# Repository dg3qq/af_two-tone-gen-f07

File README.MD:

# AF-TWO-TONE-GENERATOR

##### cc-by-sa-nc DG3QQ rodi
##### rev. mar. 2024

# Bastel-Projekt zum 14. Giessener Amateurfunk Tag

+ [expose](F07-project/_expose.md]
+ video interview by Kirk (DO3KI) [14. Gießener Amateurfunktreffen 2024 - Doppeltongenerator Bauprojekt & ARRL Prüfung USA Rufzeichen](https://www.youtube.com/watch?v=AF0V_h3_ksM)

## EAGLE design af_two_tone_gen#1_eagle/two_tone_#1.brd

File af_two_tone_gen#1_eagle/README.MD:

# Two-Tone-Generator by DG3QQ 

#### copyright: dg3qq (cc-by-sa-nc)

## PCB in EagleCad 

To get around delays, I resorted to a *free* version of EagleCad (6.xx).

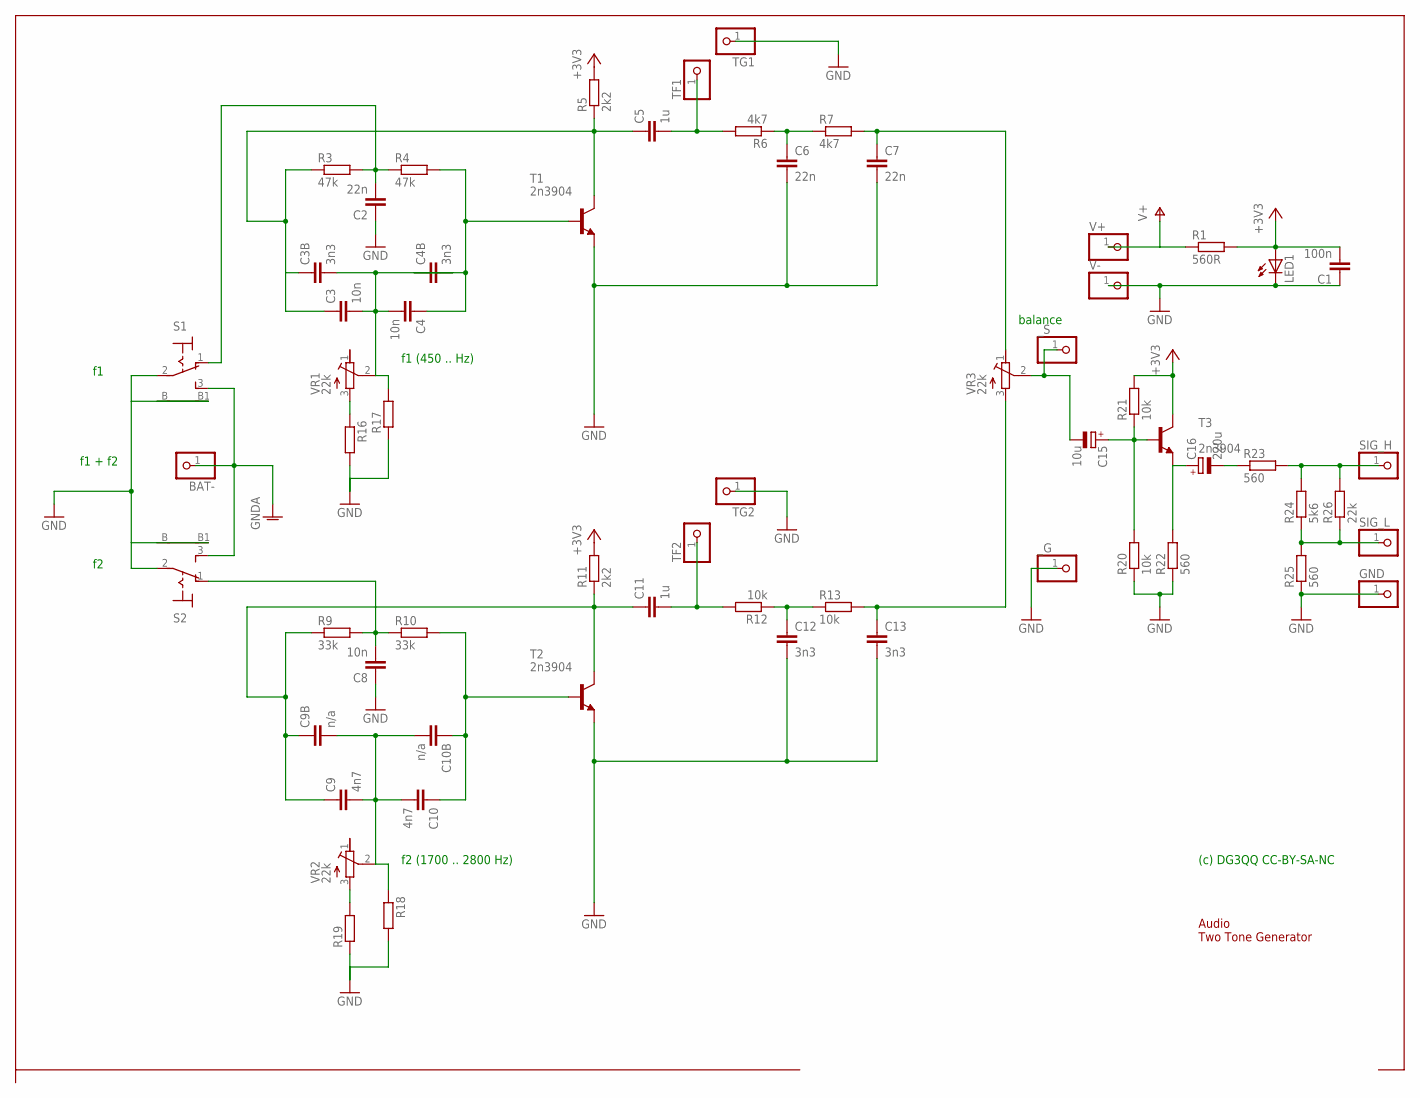
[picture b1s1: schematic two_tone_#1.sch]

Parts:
BAT-: PINHD-1X1; 1X01
C1: 100n; C025_050-025X075
C2, C6, C7: 22n; C025_050-025X075
C3, C4, C8: 10n; C025_050-025X075
C3B, C4B, C12, C13: 3n3; C025_050-025X075
C5, C11: 1u; C025_050-025X075
C9, C10: 4n7; C025_050-025X075
C9B, C10B: n/a; C025_050-025X075
C15: 10u; E2,5-5
C16: 220u; E5-10,5
GND: PINHD-1X1; 1X01
LED1: LED3MM
R1: 560R; 0207/2V
R3: 47k; 0207/10
R4: 47k; 0207/2V
R5, R11: 2k2; 0207/2V
R6, R7: 4k7; 0207/2V
R9: 33k; 0207/10
R10: 33k; 0207/2V
R12, R13, R20, R21: 10k; 0207/2V
R16, R17, R18, R19: R-EU_0207/2V; 0207/2V
R22, R23, R25: 560; 0207/2V
R24: 5k6; 0207/2V
R26: 22k; 0207/2V
S1, S2: 9070-1W
SIG_H: PINHD-1X1; 1X01
SIG_L: PINHD-1X1; 1X01
T1, T2, T3: 2n3904; TO92-EBC
TF1, TF2: PINHD-1X1; 1X01
TG1, TG2: PINHD-1X1; 1X01
V+: PINHD-1X1; 1X01
V-: PINHD-1X1; 1X01
VR1, VR2, VR3: 22k; SPINDLE_414S6
_G: PINHD-1X1; 1X01
_S: PINHD-1X1; 1X01

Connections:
+3V3: C1.2, LED1.A, R1.2, R5.2, R11.2, R21.2, T3.C
BAT-: BAT-.1, S1.3 (S), S2.3 (S)
GND: C1.1, C2.1, C6.2, C7.2, C8.1, C12.2, C13.2, GND.1, LED1.K (C), R16.2, R17.1, R18.2, R19.1, R20.1, R22.1, R25.1, S1.2, S1.B, S1.B1, S2.2, S2.B, S2.B1, T1.E, T2.E, TG1.1, TG2.1, V-.1, _G.1
unnamed: C5.2, R6.2, TF1.1
unnamed: C6.1, R6.1, R7.1
unnamed: C2.2, R3.2, R4.1, S1.1 (O)
unnamed: C4.1, C4B.1, R4.2, T1.B
unnamed: C3.1, C3B.1, C5.1, R3.1, R5.1, T1.C
unnamed: C3.2, C3B.2, C4.2, C4B.2, R17.2, VR1.2 (S)
unnamed: C7.1, R7.2, VR3.1 (A)
unnamed: C8.2, R9.2, R10.1, S2.1 (O)
unnamed: C10.1, C10B.1, R10.2, T2.B
unnamed: C9.1, C9B.1, C11.1, R9.1, R11.1, T2.C
unnamed: C9.2, C9B.2, C10.2, C10B.2, R18.1, VR2.2 (S)
unnamed: C11.2, R12.2, TF2.1
unnamed: C12.1, R12.1, R13.1
unnamed: C13.1, R13.2, VR3.3 (E)
unnamed: R19.2, VR2.3 (E)
unnamed: C15.+, R20.2, R21.1, T3.B
unnamed: C15.-, VR3.2 (S), _S.1
unnamed: R16.1, VR1.3 (E)
unnamed: C16.+, R22.2, T3.E
unnamed: C16.-, R23.1
unnamed: R23.2, R24.2, R26.2, SIG_H.1
unnamed: R24.1, R25.2, R26.1, SIG_L.1
V+: R1.1, V+.1

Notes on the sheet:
balance
f1 (450 .. Hz)
f2 (1700 .. 2800 Hz)
f1 + f2
(c) DG3QQ CC-BY-SA-NC
Audio Two Tone Generator

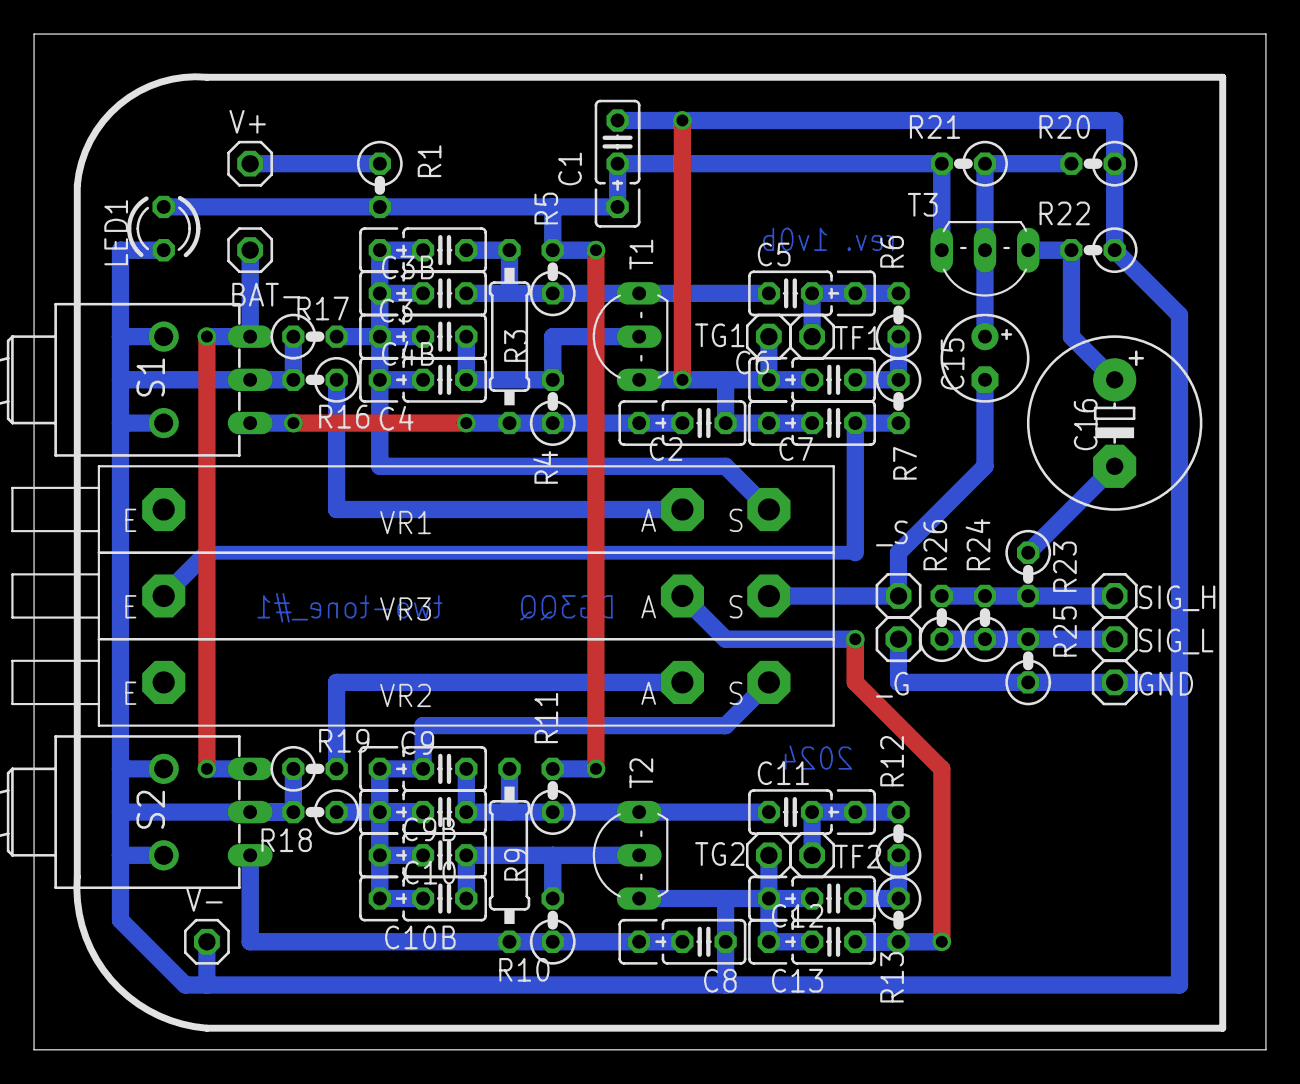
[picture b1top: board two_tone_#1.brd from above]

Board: 2 copper layers, 72.4 x 59.7 mm, 62 parts (0 on the bottom side), 26 nets.

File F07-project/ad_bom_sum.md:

# Two Tone Generator - DARC F07 Project (c) DG3QQ

#####  Doc-Rev: 20240224-1350

## Stückliste - Bill Of Materials

### Widerstände - Resitors 
| check | Qty  | type/value | id | comment |
| :---  | ---: | :--- | :--- | :--- |
| [___] | 4 | 560 0,25W | R1, R22, R23, R25 | . |
| [___] | 2 | 2k2 0,25W | R5, R11| . |
| [___] | 2 | 4k7 0,25W | R6, R7| . |
| [___] | 1 | 5k6 0,25W | R24 | . |
| [___] | 4 | 10k 0,25W | R12, R13, R20, R21| . |
| [___] | 1 | 22k 0,25W | R26 | . |
| [___] | 2 | 33k 0,25W | R9 R10| . |
| [___] | 2 | 47k 0,25W | R3, R4| . |
| [___] | 2 | 0R | R16, R19 | Brücke mit langen Enden (Harnadelform) |
|       | 2 | na | R17, R18 | . |

 
### Kondensatoren - Capacitors
| check | Qty  | type/value | id | comment |
| :---  | ---: | :--------- | :--- | :--- |
| [___] | 4 | 3n3 (332) | C3B, C4B, C12, C13 | . |
| [___] | 2 | 4n7 (472) | C9, C10| . |
| [___] | 3 | 10n (103) | C3, C4, C8 | . |
| [___] | 3 | 22n (223) | C2, C6, C7 | . |
| [___] | 1 | 100n (104) | C1 | . |
| [___] | 2 | 1µ0 (105) | C5, C11 | . |


### Elektrolyt-Kondensator - Elko
| check | Qty  | type/value | id | comment |
| :---  | ---: | :--- | :--- | :--- |
| [___] | 1 | 10µF 16V radial | C15 | . |
| [___] | 1 | 220µF 25V radial | C16 | . | 


### Transistoren - Transistors 
| check | Qty | type/value | id | comment |
| :---  | ---: | :--- | :--- | :--- |
| [___] | 3 | NPN SI-Transistor 2N3904 | T1, T2, T3 | o.ä. |


### Diodes - Dioden (LED) 
| check | Qty | type/value | id | comment |
| :---  | ---: | :--- | :--- | :--- |
| [___] | 1 | LED blue ø3mm | LED1 | EVERSTAR R3040HBDE034 |

### Potentiometer 
| check | Qty | type/value | id | comment |
| :---  | ---: | :--- | :--- | :--- |
| [___] | 3 | 22k/20turn trimpot.| VR1, VR2, VR3  | . |

### ... div.
| check | Qty | type/value  | id | comment |
| :---  | ---: | :--- | :--- | :--- |
| [___] | 2 | miniature switch SPST | S1, S2 | MTS-102-A1 |
| [___] | 3 | Buchsenleiste 1x2 pin | TF1, TF2, _S | |
| [___] | 1 | Buchsenleiste 1x3 pin | TFO | . |
| [___] | 1 | PCB                  | x1 | AllPCB |
| [___] | 1 | Batteriehalter 3xAAA | x2 | . |

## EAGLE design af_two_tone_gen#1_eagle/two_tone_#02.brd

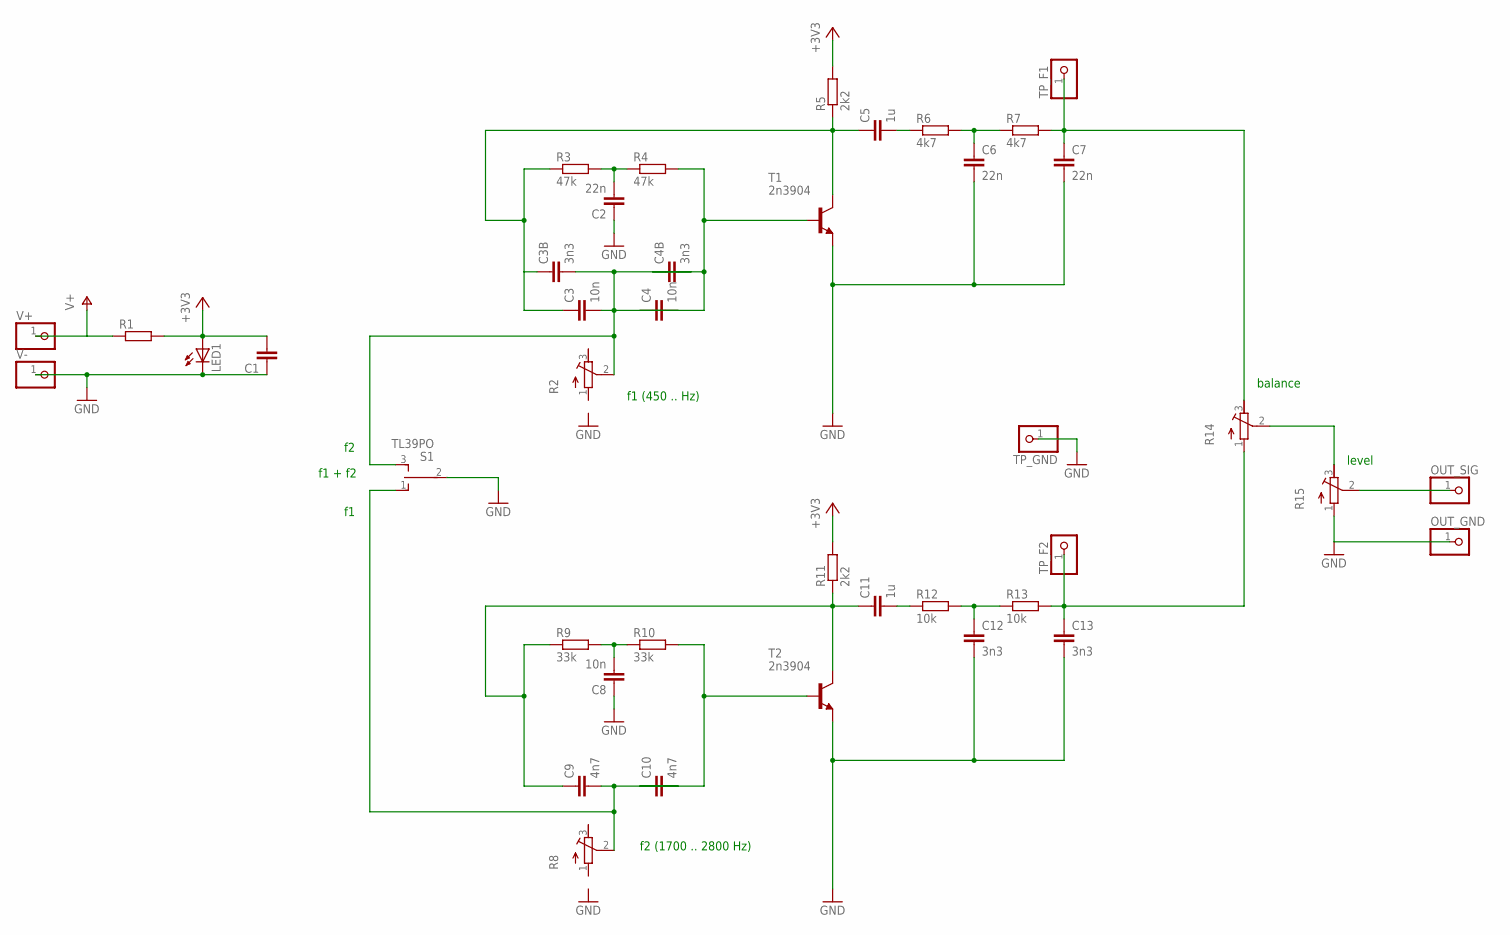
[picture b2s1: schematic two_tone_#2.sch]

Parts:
C1: C-EU025_050-025X075; C025_050-025X075
C2, C6, C7: 22n; C025_050-025X075
C3, C4, C8: 10n; C025_050-025X075
C3B, C4B, C12, C13: 3n3; C025_050-025X075
C5, C11: 1u; C025_050-025X075
C9, C10: 4n7; C025_050-025X075
LED1: LED3MM
OUT_GND: PINHD-1X1; 1X01
OUT_SIG: PINHD-1X1; 1X01
R1: R-EU_0207/2V; 0207/2V
R2, R8, R14, R15: R-TRIMM64W; RTRIM64W
R3: 47k; 0207/10
R4: 47k; 0207/5V
R5, R11: 2k2; 0207/10
R6: 4k7; 0207/10
R7: 4k7; 0207/2V
R9: 33k; 0207/10
R10: 33k; 0207/5V
R12: 10k; 0207/10
R13: 10k; 0207/2V
S1: TL39PO; TL3XPO
T1, T2: 2n3904; TO92-EBC
TP_F1, TP_F2: PINHD-1X1; 1X01
TP_GND: PINHD-1X1; 1X01
V+: PINHD-1X1; 1X01
V-: PINHD-1X1; 1X01

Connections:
+3V3: C1.2, LED1.A, R1.2, R5.2, R11.2
GND: C1.1, C2.1, C6.2, C7.2, C8.1, C12.2, C13.2, LED1.K (C), OUT_GND.1, R15.1 (E), S1.2, T1.E, T2.E, TP_GND.1, V-.1
unnamed: C5.2, R6.1
unnamed: C6.1, R6.2, R7.1
unnamed: C2.2, R3.2, R4.1
unnamed: C4.1, C4B.1, R4.2, T1.B
unnamed: C3.1, C3B.1, C5.1, R3.1, R5.1, T1.C
unnamed: C3.2, C3B.2, C4.2, C4B.2, R2.2 (S), S1.3 (S)
unnamed: C7.1, R7.2, R14.3 (A), TP_F1.1
unnamed: C8.2, R9.2, R10.1
unnamed: C10.1, R10.2, T2.B
unnamed: C9.1, C11.1, R9.1, R11.1, T2.C
unnamed: C9.2, C10.2, R8.2 (S), S1.1 (O)
unnamed: C11.2, R12.1
unnamed: C12.1, R12.2, R13.1
unnamed: C13.1, R13.2, R14.1 (E), TP_F2.1
unnamed: R14.2 (S), R15.3 (A)
unnamed: OUT_SIG.1, R15.2 (S)
V+: R1.1, V+.1

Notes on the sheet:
balance
level
f1 (450 .. Hz)
f2 (1700 .. 2800 Hz)
f1 + f2

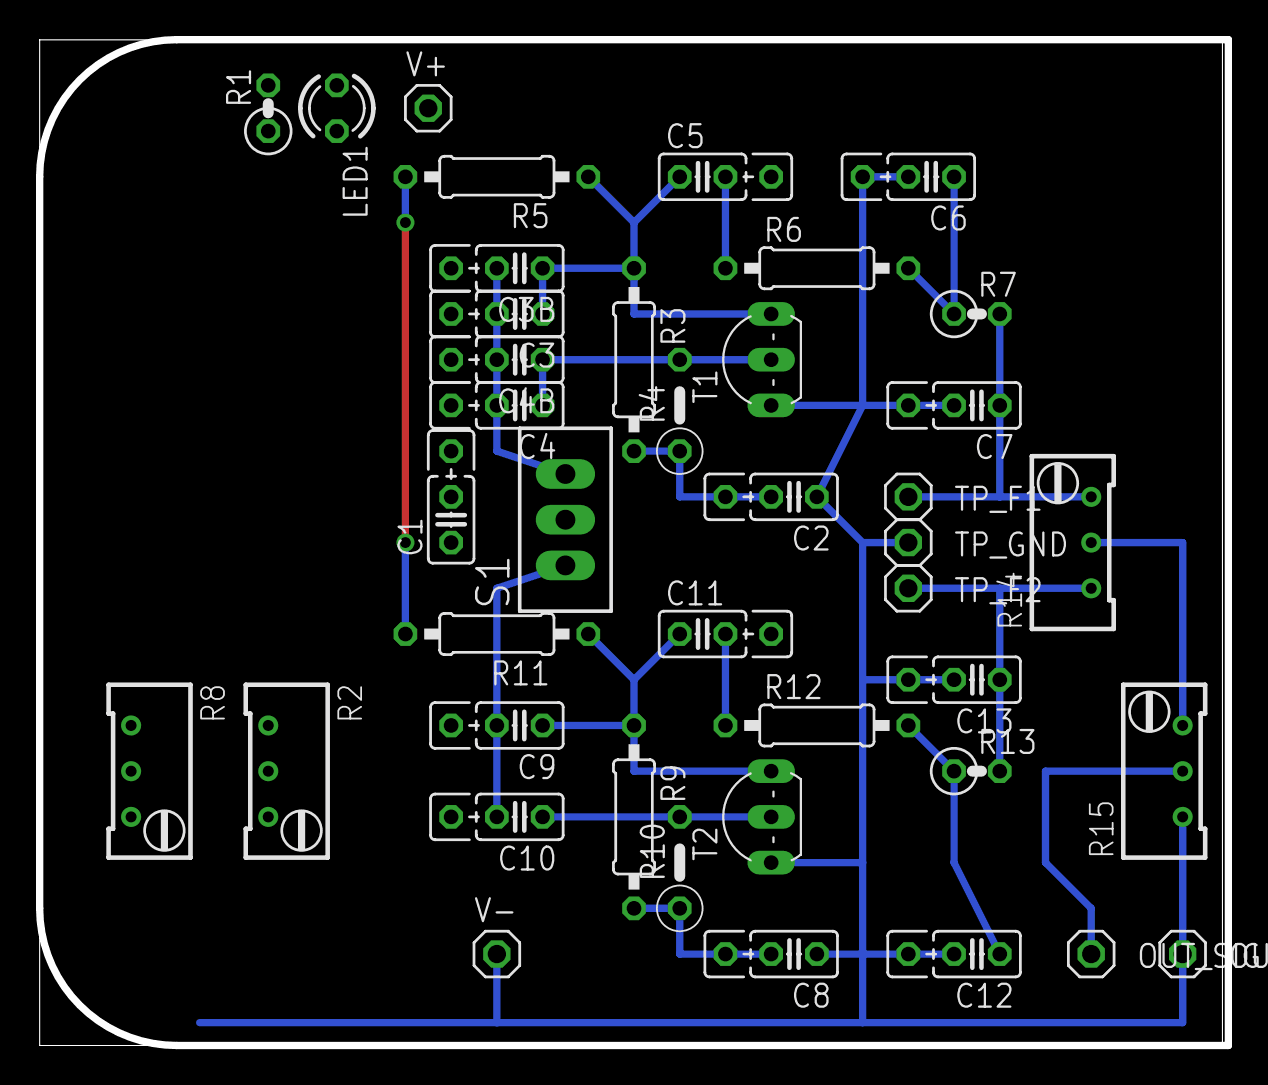
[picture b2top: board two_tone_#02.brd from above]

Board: 2 copper layers, 66.0 x 55.9 mm, 41 parts (0 on the bottom side), 19 nets.

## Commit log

2024-04-06 initial
